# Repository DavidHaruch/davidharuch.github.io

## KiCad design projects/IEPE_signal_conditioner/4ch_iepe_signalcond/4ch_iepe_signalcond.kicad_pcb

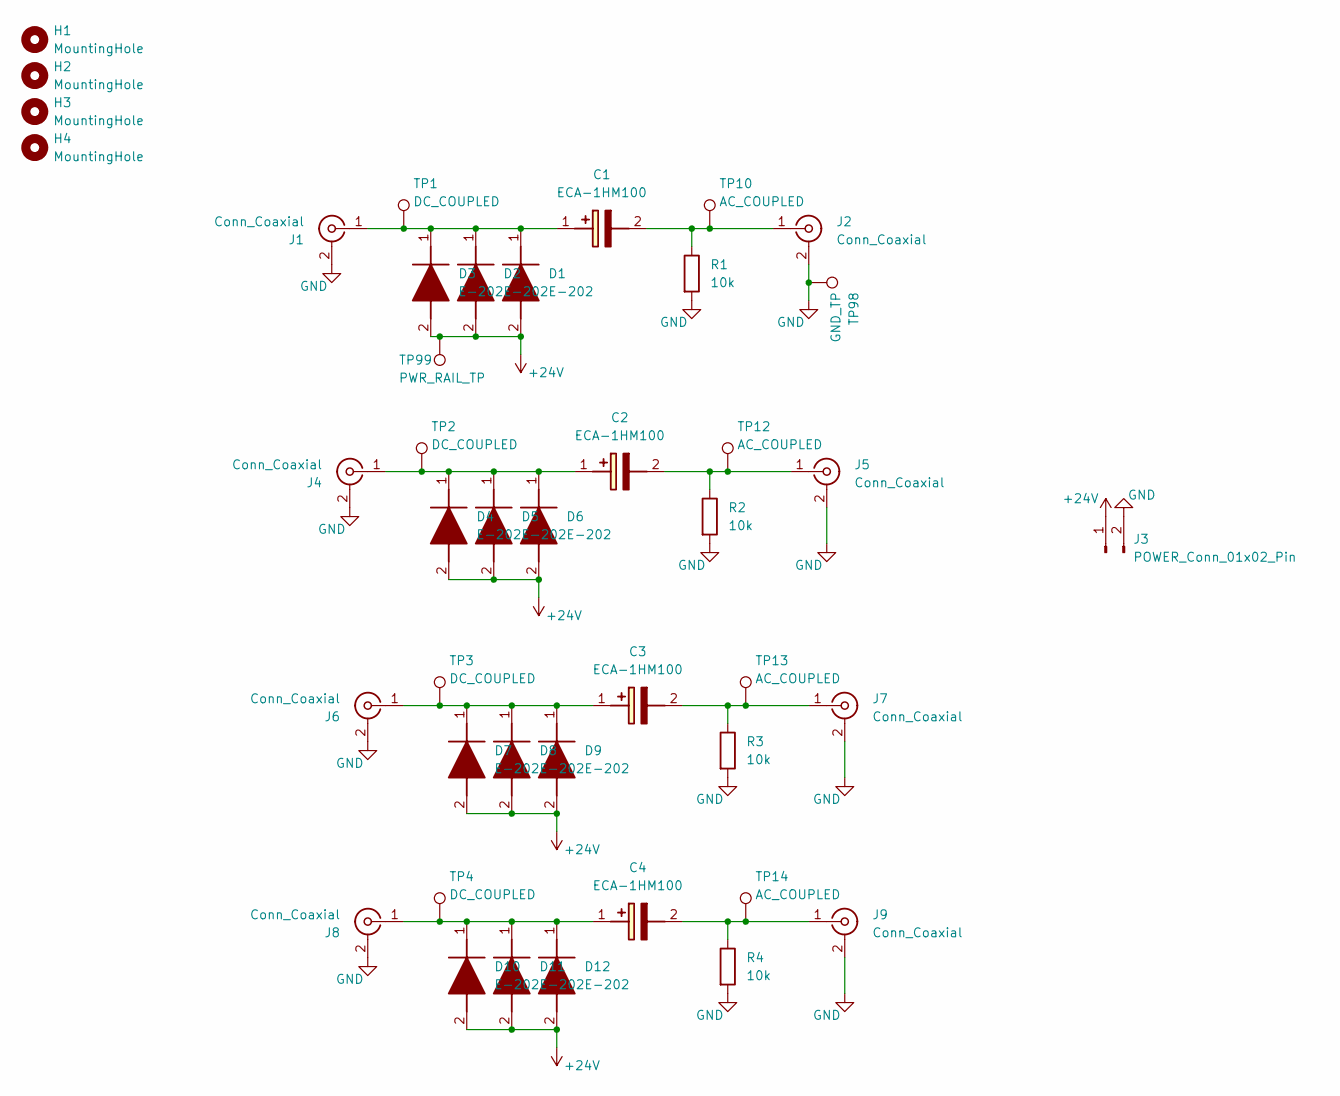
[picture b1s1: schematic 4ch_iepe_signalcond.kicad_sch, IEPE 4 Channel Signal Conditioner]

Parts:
C1, C2, C3, C4: ECA-1HM100; CAPPRD200W55D500H1200; Manufacturer_Part_Number ECA-1HM100; Mouser Part Number 667-ECA-1HM100
D1, D2, D3, D4, D5, D6, D7, D8, D9, D10, D11, D12: E-202; DIOAD1110W60L390D180; Manufacturer_Part_Number E-202; Mouser Part Number 954-E-202
H1, H2, H3, H4: MountingHole; MountingHole_3.2mm_M3
J1, J2, J4, J5, J6, J7, J8, J9: Conn_Coaxial; PinHeader_1x02_P2.00mm_Vertical
J3: POWER_Conn_01x02_Pin; PinHeader_1x02_P2.00mm_Vertical
R1, R2, R3, R4: 10k; R_Axial_DIN0207_L6.3mm_D2.5mm_P10.16mm_Horizontal
TP1, TP2, TP3, TP4: DC_COUPLED; TestPoint_Keystone_5000-5004_Miniature
TP10, TP12, TP13, TP14: AC_COUPLED; TestPoint_Keystone_5000-5004_Miniature
TP98: GND_TP; TestPoint_Keystone_5000-5004_Miniature
TP99: PWR_RAIL_TP; TestPoint_Keystone_5000-5004_Miniature

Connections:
+24V: D1.2 (A), D2.2 (A), D3.2 (A), D4.2 (A), D5.2 (A), D6.2 (A), D7.2 (A), D8.2 (A), D9.2 (A), D10.2 (A), D11.2 (A), D12.2 (A), J3.1, TP99.1 (1_1)
GND: J1.2 (Ext), J2.2 (Ext), J3.2, J4.2 (Ext), J5.2 (Ext), J6.2 (Ext), J7.2 (Ext), J8.2 (Ext), J9.2 (Ext), R1.2, R2.2, R3.2, R4.2, TP98.1 (1_1)
unnamed: C1.1 (+), D1.1 (K), D2.1 (K), D3.1 (K), J1.1 (In), TP1.1 (1_1)
unnamed: C1.2 (-), J2.1 (In), R1.1, TP10.1 (1_1)
unnamed: C2.1 (+), D4.1 (K), D5.1 (K), D6.1 (K), J4.1 (In), TP2.1 (1_1)
unnamed: C2.2 (-), J5.1 (In), R2.1, TP12.1 (1_1)
unnamed: C3.1 (+), D7.1 (K), D8.1 (K), D9.1 (K), J6.1 (In), TP3.1 (1_1)
unnamed: C3.2 (-), J7.1 (In), R3.1, TP13.1 (1_1)
unnamed: C4.1 (+), D10.1 (K), D11.1 (K), D12.1 (K), J8.1 (In), TP4.1 (1_1)
unnamed: C4.2 (-), J9.1 (In), R4.1, TP14.1 (1_1)

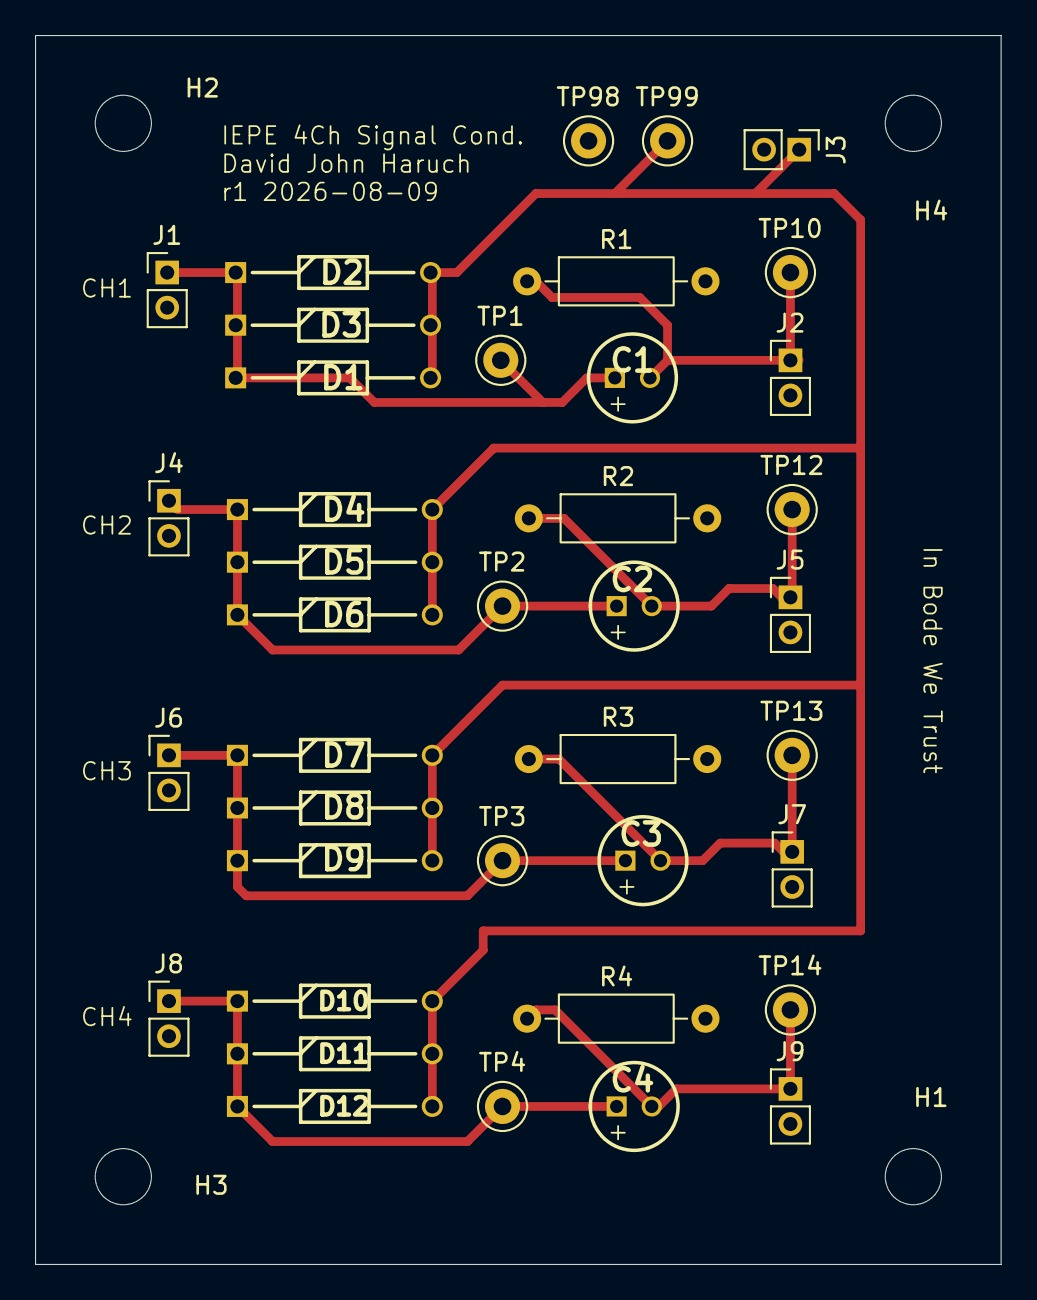
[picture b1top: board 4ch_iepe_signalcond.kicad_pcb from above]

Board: 2 copper layers, 55.0 x 70.0 mm, 43 parts (0 on the bottom side), 10 nets.

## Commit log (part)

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2022-12-23 Add files via upload
    FSAE drawings
2022-12-23 Add files via upload
    3 view FSAE DR21
2023-12-18 Add VCM page
2023-12-18 fix percent sign
2023-12-23 motor material cost page
2024-07-25 iron core page
2024-10-21 fx36 project
2024-10-21 typo fix
2025-02-18 tmd fea project
2025-02-24 ul12 lm post
2025-06-15 mag counterbalance
2025-06-20 magcbalance
2025-07-28 UX9 Rev Eng
2025-10-07 semi precision page
2025-10-31 ux9 update
2025-11-10 nikon nsr322
2026-03-06 fox 36 dyno data post
2026-03-15 2020 enduro long chainstay
2026-03-30 temp control
2026-06-23 lm3886_pt1
